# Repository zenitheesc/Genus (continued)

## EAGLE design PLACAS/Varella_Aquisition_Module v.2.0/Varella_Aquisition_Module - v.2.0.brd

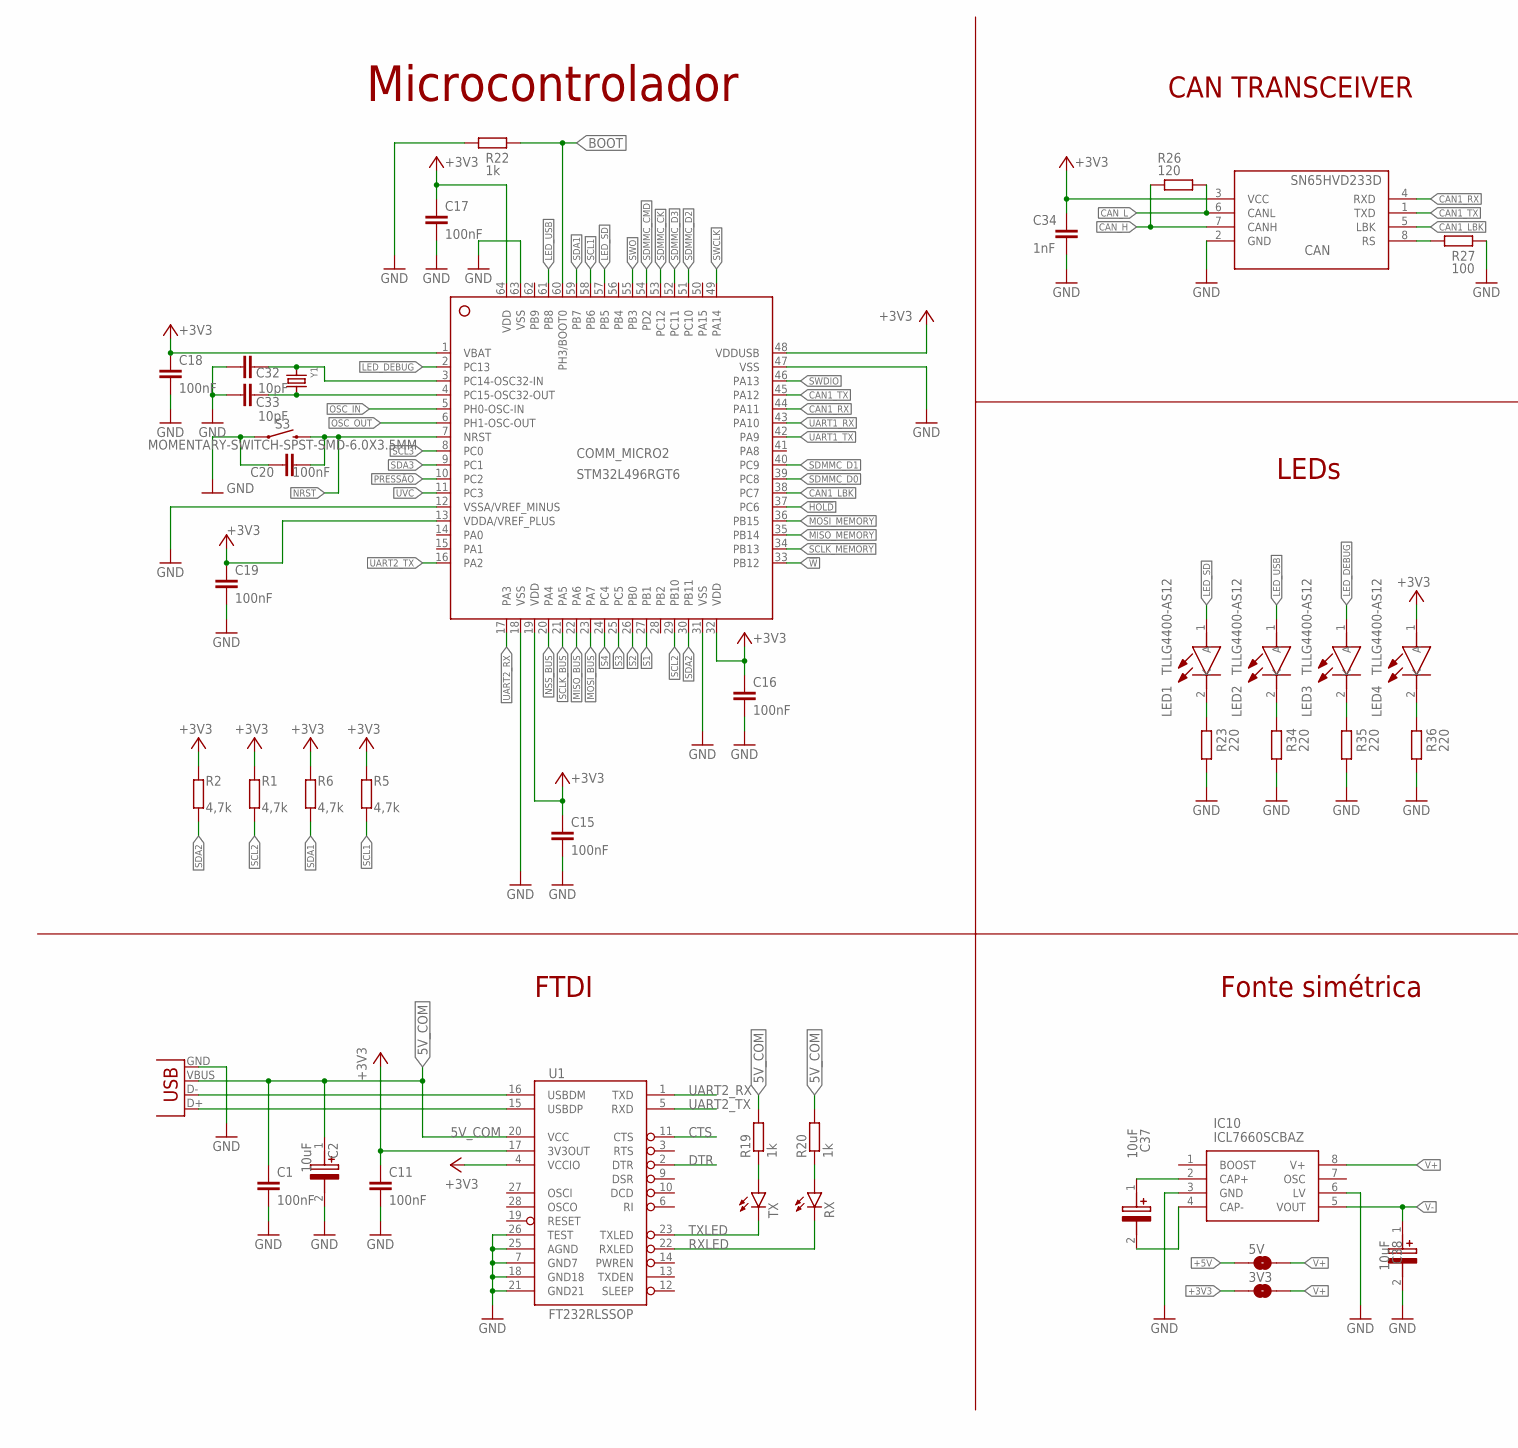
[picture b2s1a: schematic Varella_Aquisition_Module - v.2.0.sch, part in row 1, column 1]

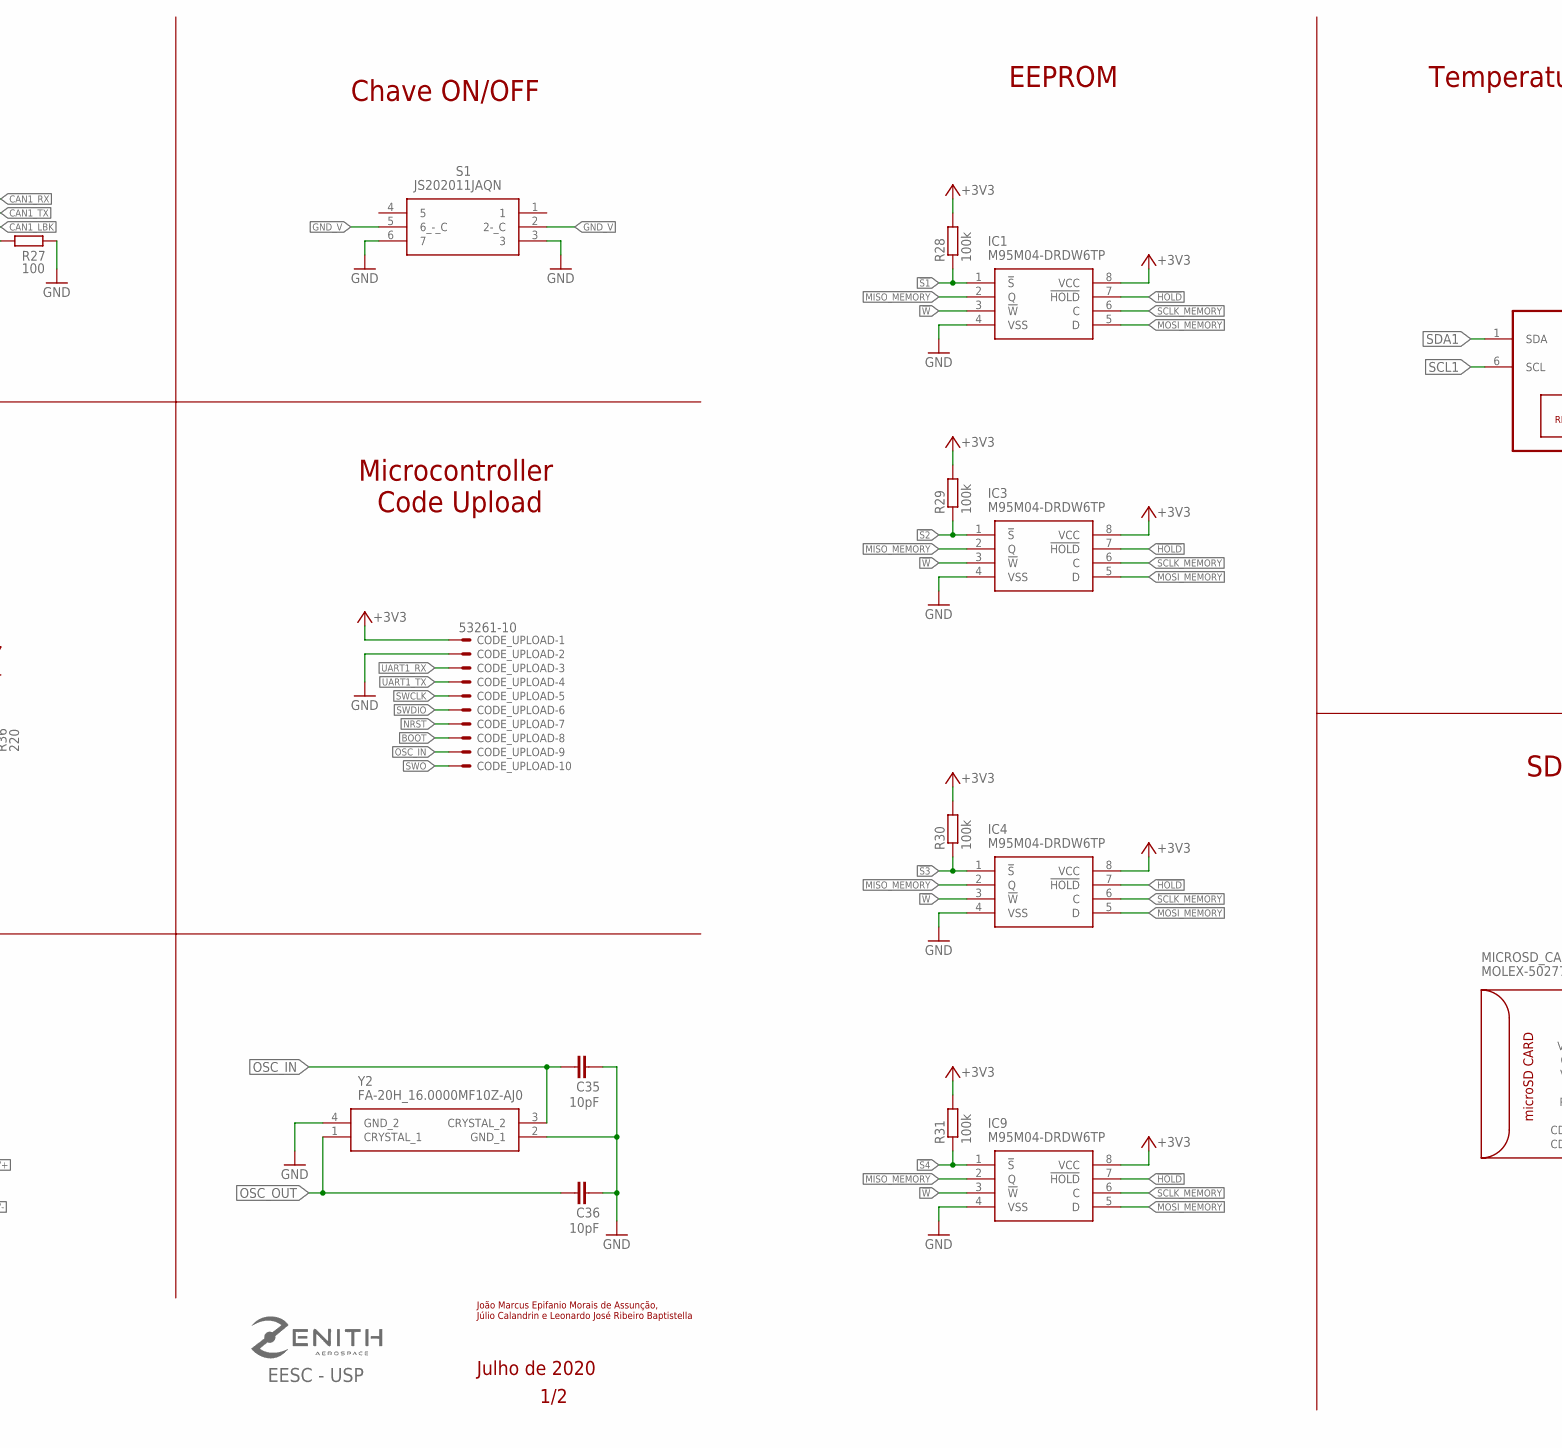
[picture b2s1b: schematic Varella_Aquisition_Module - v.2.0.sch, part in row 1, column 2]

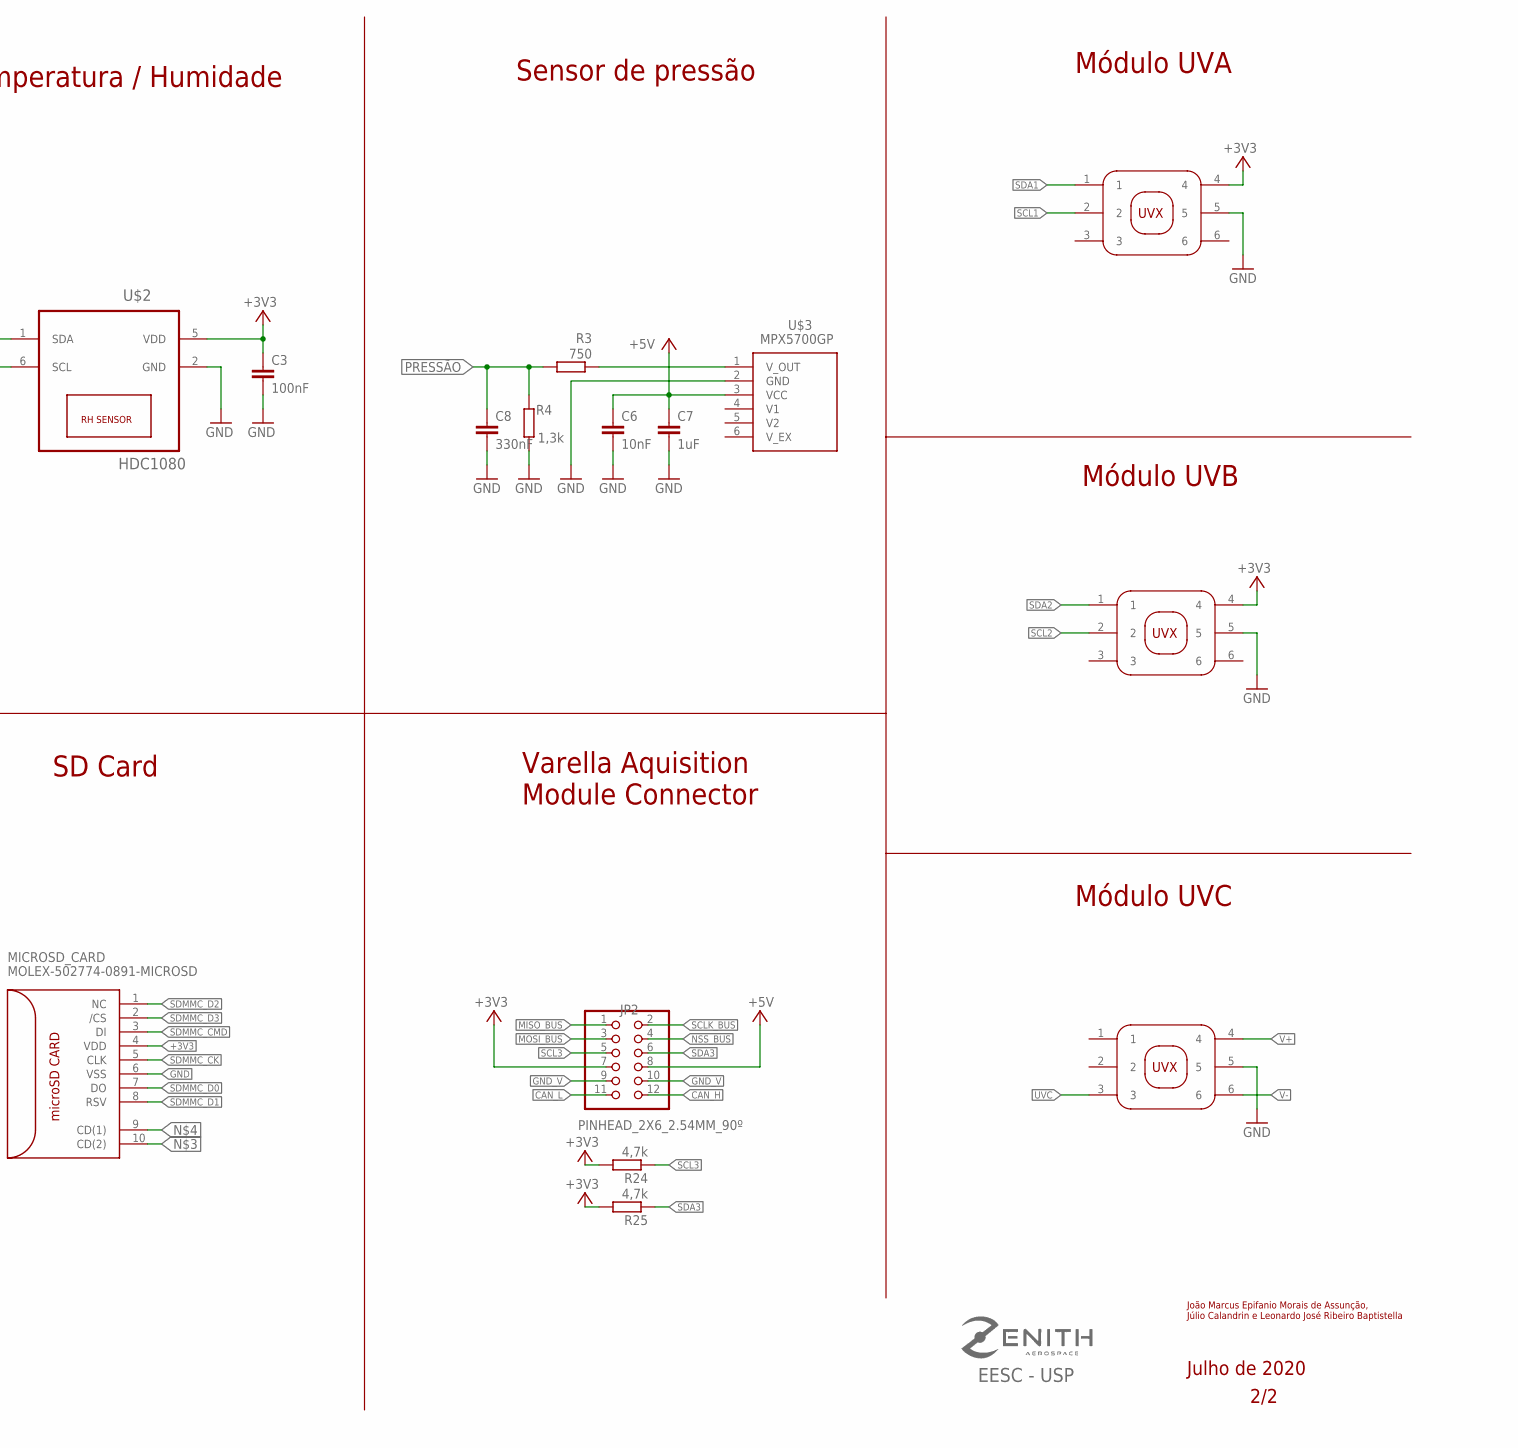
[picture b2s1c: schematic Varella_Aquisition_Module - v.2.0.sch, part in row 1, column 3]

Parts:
3V3, 5V: SMD-JUMPER-2
C1, C3, C11, C15, C16, C17, C18, C19, C20: 100nF; C0805
C2, C37, C38: 10uF; CAPAE430X610N
C6: 10nF; C0805
C7: 1uF; C0805
C8: 330nF; C0805
C32, C33, C35, C36: 10pF; C0805
C34: 1nF; C1206
CAN: SN65HVD233D; SOIC8
CODE_UPLOAD: 53261-10
COMM_MICRO2: STM32L496RGT6; LQFP64_10X10
IC1, IC3, IC4, IC9: M95M04-DRDW6TP; SOP65P640X120-8N
IC10: ICL7660SCBAZ; SOIC127P600X175-8N@1
JP2: PINHEAD_2X6_2.54MM_90º
LED1, LED2, LED3, LED4: TLLG4400-AS12; TLLG4400AS12
MICROSD_CARD: MOLEX-502774-0891-MICROSD
R1, R2, R5, R6, R24, R25: 4,7k; R0805
R3: 750; R0805
R4: 1,3k; R0805
R19, R20, R22: 1k; R0805
R23, R34, R35, R36: 220; R0805
R26: 120; R1206
R27: 100; R0805
R28, R29, R30, R31: 100k; R0805
RX: LEDCHIPLED_0805; CHIPLED_0805
S1: JS202011JAQN
S3: MOMENTARY-SWITCH-SPST-SMD-6.0X3.5MM; TACTILE_SWITCH_SMD_6.0X3.5MM
TX: LEDCHIPLED_0805; CHIPLED_0805
U1: FT232RLSSOP; SSOP28DB
U$2: HDC1080; TI-S-PWSON-N6
U$3: MPX5700GP
U$6, U$7, U$8: MODULO_UV
X2: USB-SMD-NS; USB-MINIB-NOSTOP
Y1: CRYSTAL8X3.8SMT; CRYSTAL_8X3.8
Y2: FA-20H_16.0000MF10Z-AJ0; FA20H160000MF12ZAC3

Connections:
5V_COM: C1.1, C2.1 (+), R19.2, R20.2, U1.20 (VCC), X2.VBUS
!HOLD: COMM_MICRO2.37 (PC6), IC1.7 (!HOLD), IC3.7 (!HOLD), IC4.7 (!HOLD), IC9.7 (!HOLD)
!S1: COMM_MICRO2.27 (PB1), IC1.1 (!S), R28.1
!S2: COMM_MICRO2.26 (PB0), IC3.1 (!S), R29.1
!S3: COMM_MICRO2.25 (PC5), IC4.1 (!S), R30.1
!S4: COMM_MICRO2.24 (PC4), IC9.1 (!S), R31.1
!W: COMM_MICRO2.33 (PB12), IC1.3 (!W), IC3.3 (!W), IC4.3 (!W), IC9.3 (!W)
+3V3: 3V3.2, C3.1, C11.1, C15.1, C16.1, C17.1, C18.1, C19.1, C34.1, CAN.3 (VCC), CODE_UPLOAD.1, COMM_MICRO2.1 (VBAT), COMM_MICRO2.13 (VDDA/VREF_PLUS), COMM_MICRO2.19 (VDD), COMM_MICRO2.32 (VDD), COMM_MICRO2.48 (VDDUSB), COMM_MICRO2.64 (VDD), IC1.8 (VCC), IC3.8 (VCC), IC4.8 (VCC), IC9.8 (VCC), JP2.7, LED4.1 (A), MICROSD_CARD.4 (VDD), R1.2, R2.2, R5.2, R6.2, R24.2, R25.2, R28.2, R29.2, R30.2, R31.2, U1.4 (VCCIO), U1.17 (3V3OUT), U$2.5 (VDD), U$6.4, U$7.4
+5V: 5V.2, C6.1, C7.1, JP2.8, U$3.3 (VCC)
BOOT: CODE_UPLOAD.8, COMM_MICRO2.60 (PH3/BOOT0), R22.1
CAN1_LBK: CAN.5 (LBK), COMM_MICRO2.38 (PC7)
CAN1_RX: CAN.4 (RXD), COMM_MICRO2.44 (PA11)
CAN1_TX: CAN.1 (TXD), COMM_MICRO2.45 (PA12)
CAN_H: CAN.7 (CANH), JP2.12, R26.1
CAN_L: CAN.6 (CANL), JP2.11, R26.2
CRYSTAL1: C32.2, COMM_MICRO2.3 (PC14-OSC32-IN), Y1.P$1 (1)
CTS: U1.11 (CTS)
DTR: U1.2 (DTR)
GND: C1.2, C2.2 (-), C3.2, C6.2, C7.2, C8.2, C11.2, C15.2, C16.2, C17.2, C18.2, C19.2, C20.1, C32.1, C33.1, C34.2, C35.2, C36.2, C38.2 (-), CAN.2 (GND), CODE_UPLOAD.2, COMM_MICRO2.12 (VSSA/VREF_MINUS), COMM_MICRO2.18 (VSS), COMM_MICRO2.31 (VSS), COMM_MICRO2.47 (VSS), COMM_MICRO2.63 (VSS), IC1.4 (VSS), IC3.4 (VSS), IC4.4 (VSS), IC9.4 (VSS), IC10.3 (GND), IC10.6 (LV), MICROSD_CARD.6 (VSS), R4.2, R22.2, R23.1, R27.1, R34.1, R35.1, R36.1, S1.3, S1.6 (7), S3.1, U1.7 (GND7), U1.18 (GND18), U1.21 (GND21), U1.25 (AGND), U1.26 (TEST), U$2.2 (GND), U$6.5, U$7.5, U$8.5, X2.GND, Y2.2 (GND_1), Y2.4 (GND_2)
GND_V: JP2.9, JP2.10, S1.2 (2-_C), S1.5 (6_-_C)
LED_DEBUG: COMM_MICRO2.2 (PC13), LED3.1 (A)
LED_SD: COMM_MICRO2.57 (PB5), LED1.1 (A)
LED_USB: COMM_MICRO2.61 (PB8), LED2.1 (A)
MISO_BUS: COMM_MICRO2.22 (PA6), JP2.1
MISO_MEMORY: COMM_MICRO2.35 (PB14), IC1.2 (Q), IC3.2 (Q), IC4.2 (Q), IC9.2 (Q)
MOSI_BUS: COMM_MICRO2.23 (PA7), JP2.3
MOSI_MEMORY: COMM_MICRO2.36 (PB15), IC1.5 (D), IC3.5 (D), IC4.5 (D), IC9.5 (D)
unnamed: R3.1, U$3.1 (V_OUT)
unnamed: C33.2, COMM_MICRO2.4 (PC15-OSC32-OUT), Y1.P$4 (2)
unnamed: CAN.8 (RS), R27.2
unnamed: C37.1 (+), IC10.2 (CAP+)
unnamed: C37.2 (-), IC10.4 (CAP-)
unnamed: LED1.2 (K), R23.2
unnamed: LED2.2 (K), R34.2
unnamed: LED3.2 (K), R35.2
unnamed: LED4.2 (K), R36.2
NRST: C20.2, CODE_UPLOAD.7, COMM_MICRO2.7 (NRST), S3.2
NSS_BUS: COMM_MICRO2.20 (PA4), JP2.4
OSC_IN: C35.1, CODE_UPLOAD.9, COMM_MICRO2.5 (PH0-OSC-IN), Y2.3 (CRYSTAL_2)
OSC_OUT: C36.1, COMM_MICRO2.6 (PH1-OSC-OUT), Y2.1 (CRYSTAL_1)
PRESSÃO: C8.1, COMM_MICRO2.10 (PC2), R3.2, R4.1
RXL: R20.1, RX.A
RXLED: RX.C, U1.22 (RXLED)
SCL1: COMM_MICRO2.58 (PB6), R5.1, U$2.6 (SCL), U$6.2
SCL2: COMM_MICRO2.29 (PB10), R1.1, U$7.2
SCL3: COMM_MICRO2.8 (PC0), JP2.5, R24.1
SCLK_BUS: COMM_MICRO2.21 (PA5), JP2.2
SCLK_MEMORY: COMM_MICRO2.34 (PB13), IC1.6 (C), IC3.6 (C), IC4.6 (C), IC9.6 (C)
SDA1: COMM_MICRO2.59 (PB7), R6.1, U$2.1 (SDA), U$6.1
SDA2: COMM_MICRO2.30 (PB11), R2.1, U$7.1
SDA3: COMM_MICRO2.9 (PC1), JP2.6, R25.1
SDMMC_CK: COMM_MICRO2.53 (PC12), MICROSD_CARD.5 (CLK)
SDMMC_CMD: COMM_MICRO2.54 (PD2), MICROSD_CARD.3 (DI)
SDMMC_D0: COMM_MICRO2.39 (PC8), MICROSD_CARD.7 (DO)
SDMMC_D1: COMM_MICRO2.40 (PC9), MICROSD_CARD.8 (RSV)
SDMMC_D2: COMM_MICRO2.51 (PC10), MICROSD_CARD.1 (NC)
SDMMC_D3: COMM_MICRO2.52 (PC11), MICROSD_CARD.2 (/CS)
SWCLK: CODE_UPLOAD.5, COMM_MICRO2.49 (PA14)
SWDIO: CODE_UPLOAD.6, COMM_MICRO2.46 (PA13)
SWO: CODE_UPLOAD.10, COMM_MICRO2.55 (PB3)
TXL: R19.1, TX.A
TXLED: TX.C, U1.23 (TXLED)
UART1_RX: CODE_UPLOAD.3, COMM_MICRO2.43 (PA10)
UART1_TX: CODE_UPLOAD.4, COMM_MICRO2.42 (PA9)
UART2_RX: COMM_MICRO2.17 (PA3), U1.1 (TXD)
UART2_TX: COMM_MICRO2.16 (PA2), U1.5 (RXD)
USB_D+2: U1.15 (USBDP), X2.D+
USB_D-2: U1.16 (USBDM), X2.D-
UVC: COMM_MICRO2.11 (PC3), U$8.3
V+: 3V3.1, 5V.1, IC10.8 (V+), U$8.4
V-: C38.1 (+), IC10.5 (VOUT), U$8.6

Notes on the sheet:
C:/Users/marcu/Desktop/Ensino Superior/Graduação - Eng Elétrica/Zenith/zenith-v2.bmp
Microcontrolador
CAN TRANSCEIVER
Microcontroller Code Upload
SD Card
Varella Aquisition Module Connector
EEPROM
FTDI
Temperatura / Humidade
Fonte simétrica
LEDs
Sensor de pressão
Chave ON/OFF
Módulo UVA
Módulo UVB
Módulo UVC
EESC - USP
Julho de 2020
2/2
1/2
João Marcus Epifanio Morais de Assunção, Júlio Calandrin e Leonardo José Ribeiro Baptistella

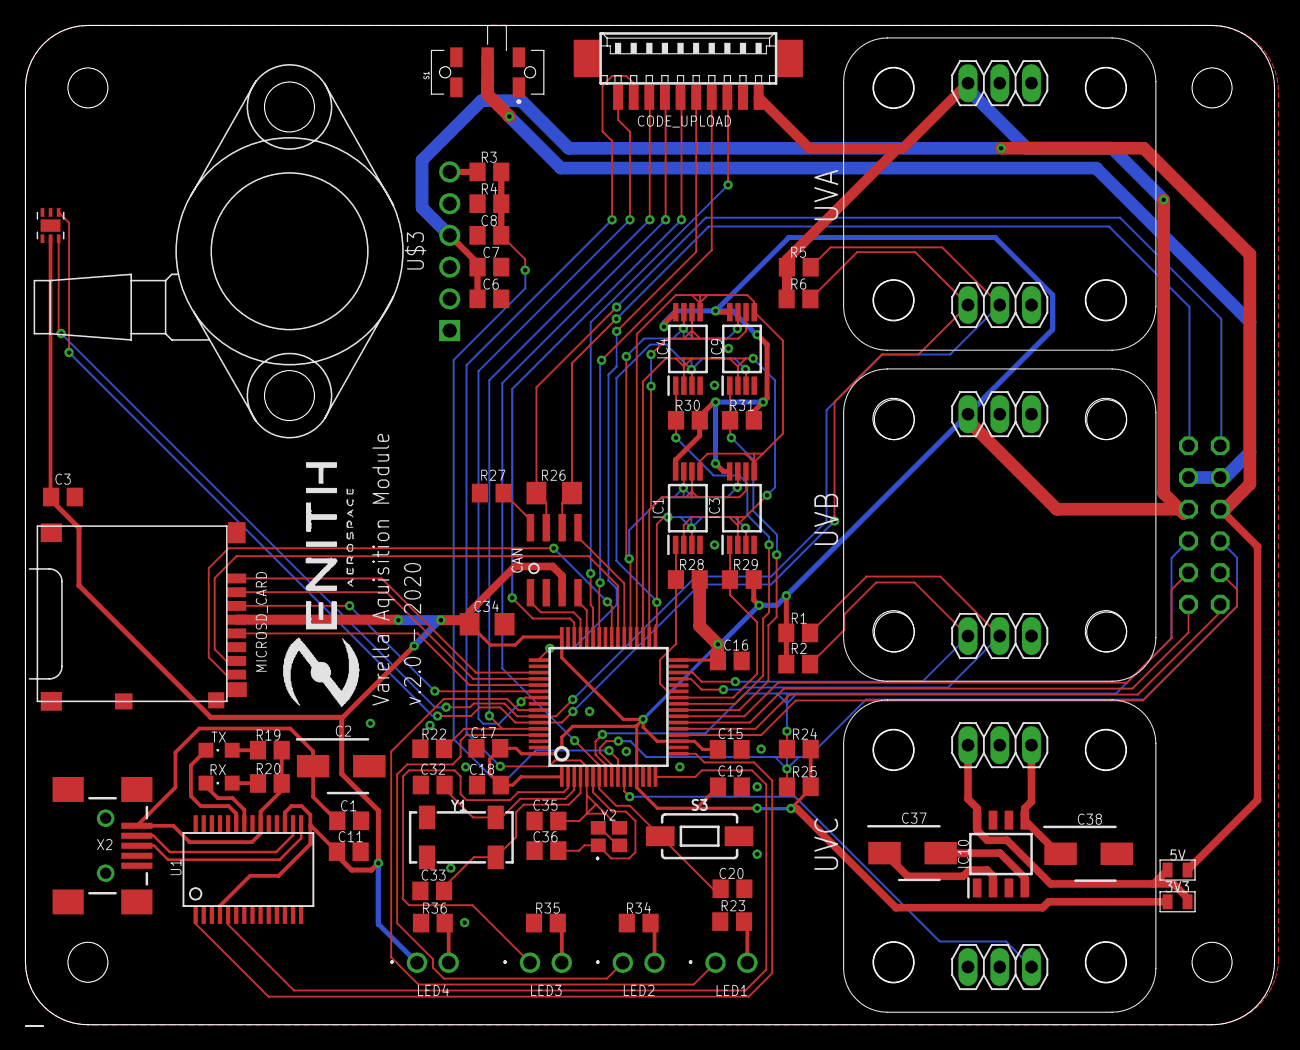
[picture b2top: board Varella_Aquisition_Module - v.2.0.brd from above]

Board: 2 copper layers, 100.0 x 80.0 mm, 70 parts (1 on the bottom side), 69 nets.

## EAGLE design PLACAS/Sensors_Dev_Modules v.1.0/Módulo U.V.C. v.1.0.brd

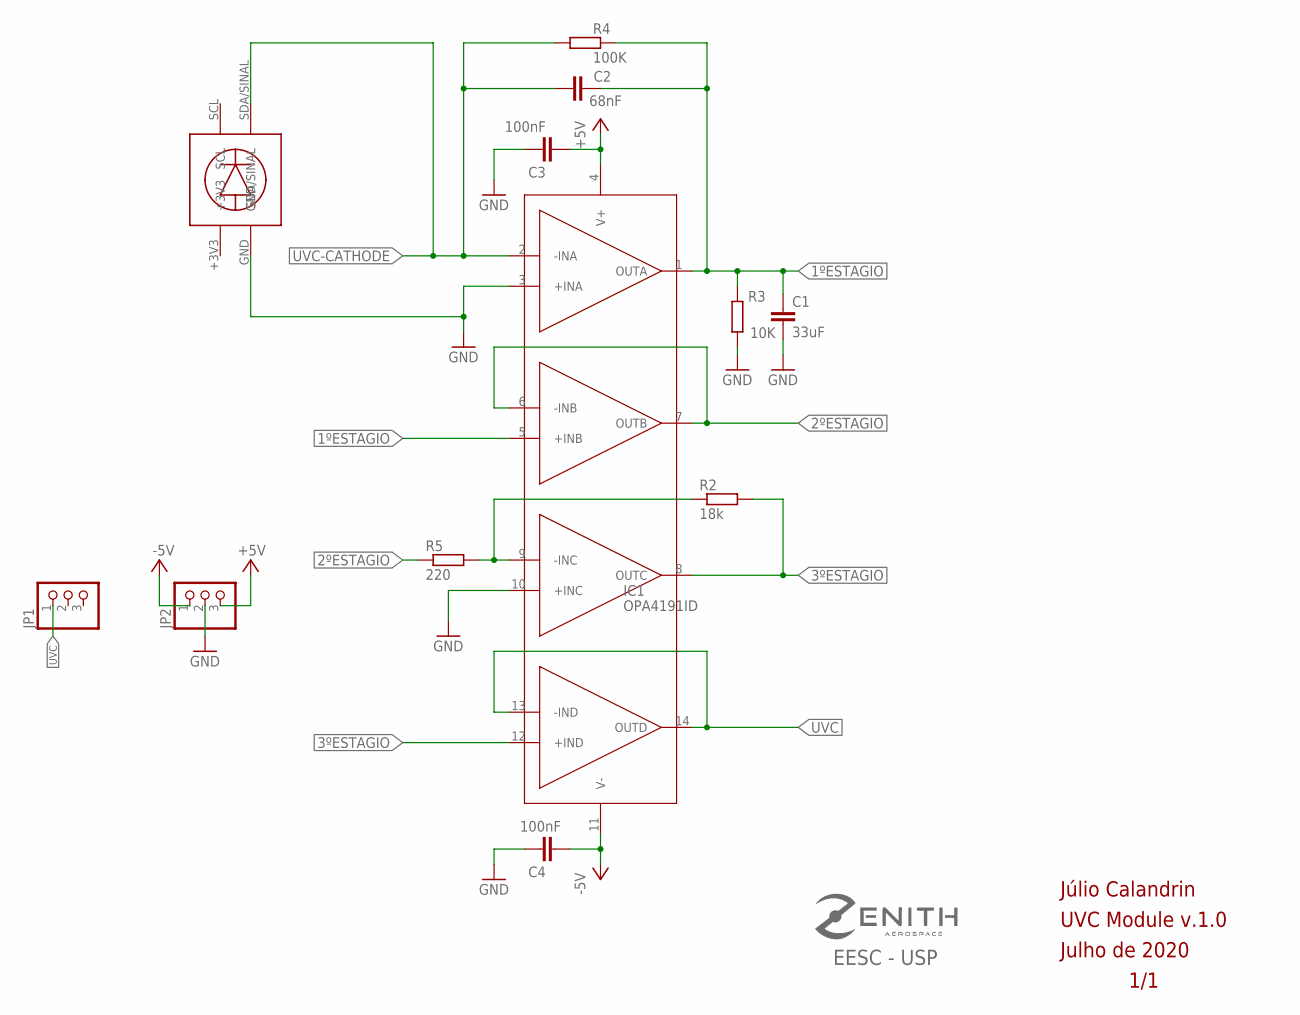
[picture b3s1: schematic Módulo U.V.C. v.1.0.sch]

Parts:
C1: 33uF; C0805
C2: 68nF; C0805
C3, C4: 100nF; C0805
IC1: OPA4191ID; D14_TEX
JP1, JP2: PINHD-1X3; 1X03
R2: 18k; R0805
R3: 10K; R0805
R4: 100K; R0805
R5: 220; R0805
U$3: UNIVERSAL_BREAKOUT; UNIVERSAL_PADS

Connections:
1ºESTAGIO: C1.1, C2.2, IC1.1 (OUTA), IC1.5 (+INB), R3.2, R4.2
2ºESTAGIO: IC1.6 (-INB), IC1.7 (OUTB), R5.1
3ºESTAGIO: IC1.8 (OUTC), IC1.12 (+IND), R2.2
+5V: C3.1, IC1.4 (V+), JP2.3
-5V: C4.1, IC1.11 (V-), JP2.1
GND: C1.2, C3.2, C4.2, IC1.3 (+INA), IC1.10 (+INC), JP2.2, R3.1, U$3.GND
unnamed: IC1.9 (-INC), R2.1, R5.2
UVC: IC1.13 (-IND), IC1.14 (OUTD), JP1.1
UVC-CATHODE: C2.1, IC1.2 (-INA), R4.1, U$3.SDA/SINAL

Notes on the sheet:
EESC - USP
Júlio Calandrin
Julho de 2020
1/1
UVC Module v.1.0

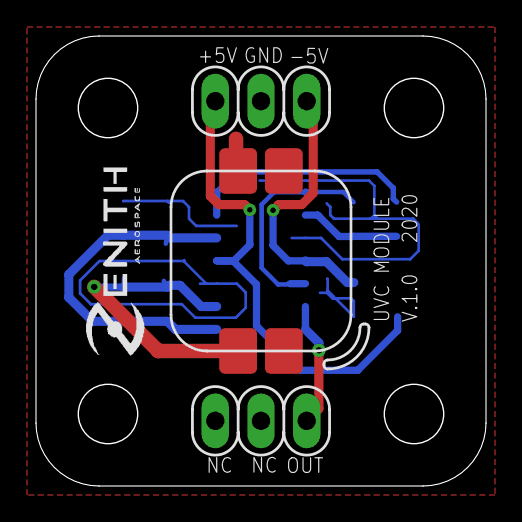
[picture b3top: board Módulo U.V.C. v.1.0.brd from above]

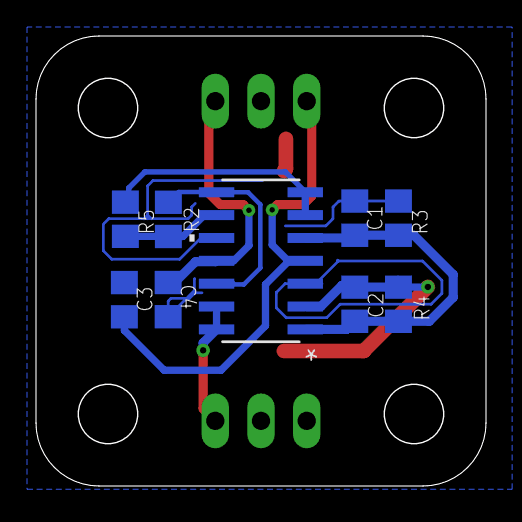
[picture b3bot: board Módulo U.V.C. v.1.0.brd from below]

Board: 2 copper layers, 25.0 x 25.0 mm, 12 parts (9 on the bottom side), 9 nets.

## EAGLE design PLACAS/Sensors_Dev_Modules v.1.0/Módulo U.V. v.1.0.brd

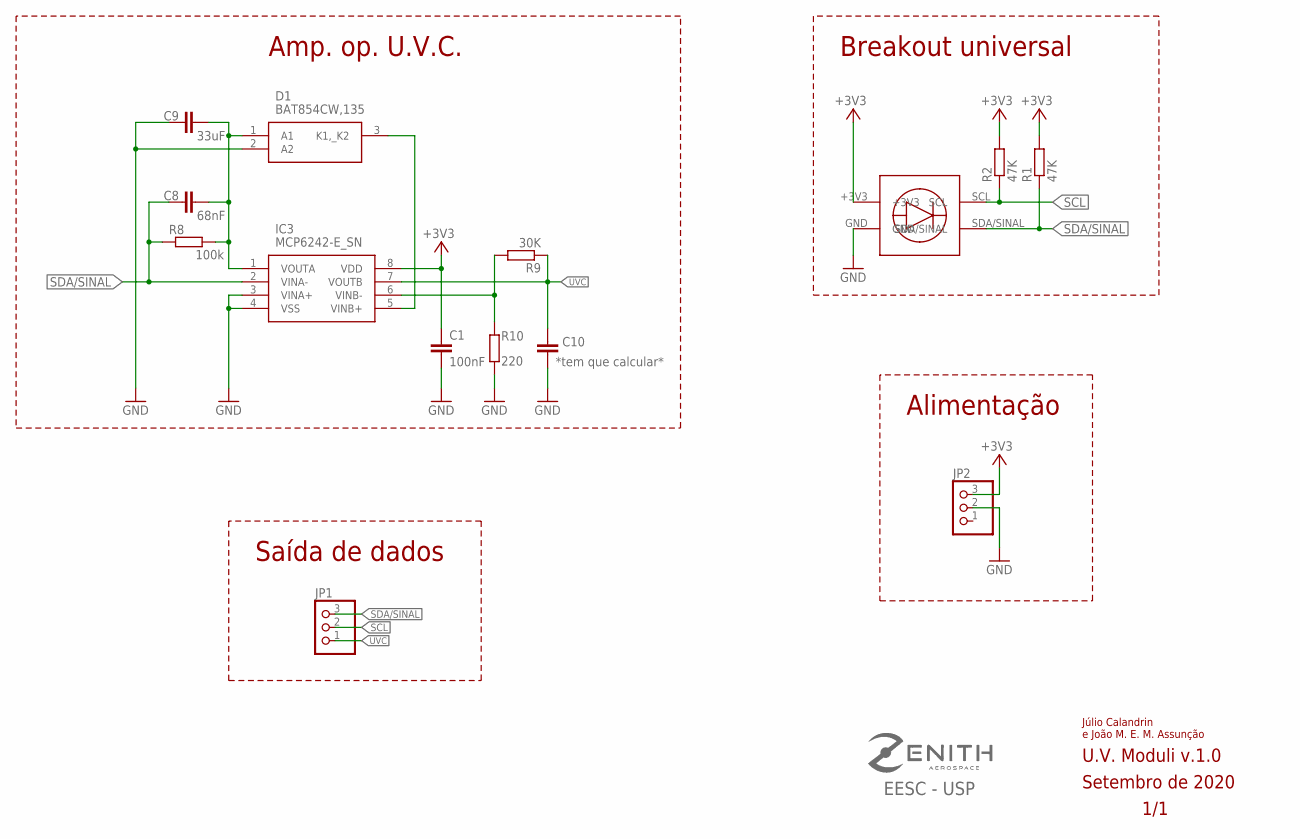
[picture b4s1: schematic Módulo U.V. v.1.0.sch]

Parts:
C1: 100nF; C0805
C8: 68nF; C0805
C9: 33uF; C0805
C10: *tem que calcular*; C0805
D1: BAT854CW,135; SOT65P210X110-3N
IC3: MCP6242-E_SN; SOIC127P600X175-8N
JP1, JP2: PINHD-1X3; 1X03
R1, R2: 47K; R0805
R8: 100k; R0805
R9: 30K; R0805
R10: 220; R0805
U$1: UNIVERSAL_BREAKOUT; UNIVERSAL_PADS

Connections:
+3V3: C1.1, IC3.8 (VDD), JP2.3, R1.2, R2.2, U$1.+3V3
GND: C1.2, C9.2, C10.2, D1.2 (A2), IC3.3 (VINA+), IC3.4 (VSS), JP2.2, R10.1, U$1.GND
unnamed: C8.2, C9.1, D1.1 (A1), IC3.1 (VOUTA), R8.2
unnamed: D1.3 (K1,_K2), IC3.5 (VINB+)
unnamed: IC3.6 (VINB-), R9.2, R10.2
SCL: JP1.2, R2.1, U$1.SCL
SDA/SINAL: C8.1, IC3.2 (VINA-), JP1.3, R1.1, R8.1, U$1.SDA/SINAL
UVC: C10.1, IC3.7 (VOUTB), JP1.1, R9.1

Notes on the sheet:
EESC - USP
Júlio Calandrin e João M. E. M. Assunção
Setembro de 2020
1/1
U.V. Moduli v.1.0
Amp. op. U.V.C.
Breakout universal
Saída de dados
Alimentação

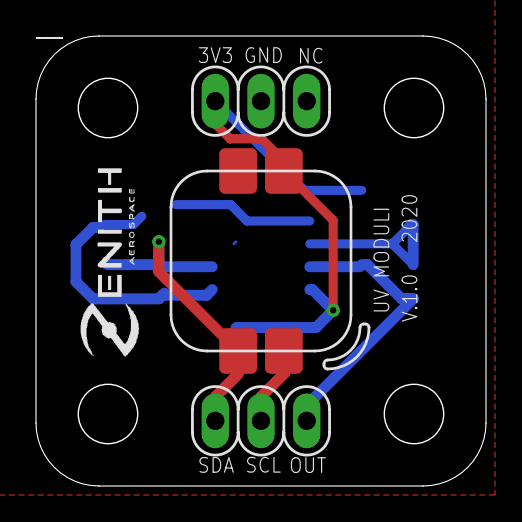
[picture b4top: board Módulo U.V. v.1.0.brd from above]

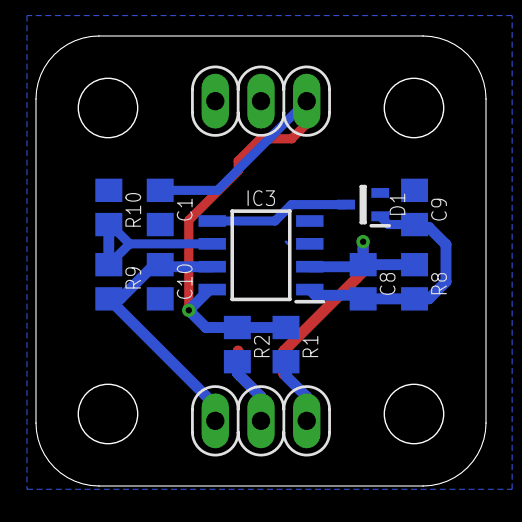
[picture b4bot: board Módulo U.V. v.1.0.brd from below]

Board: 2 copper layers, 25.0 x 25.0 mm, 14 parts (11 on the bottom side), 8 nets.

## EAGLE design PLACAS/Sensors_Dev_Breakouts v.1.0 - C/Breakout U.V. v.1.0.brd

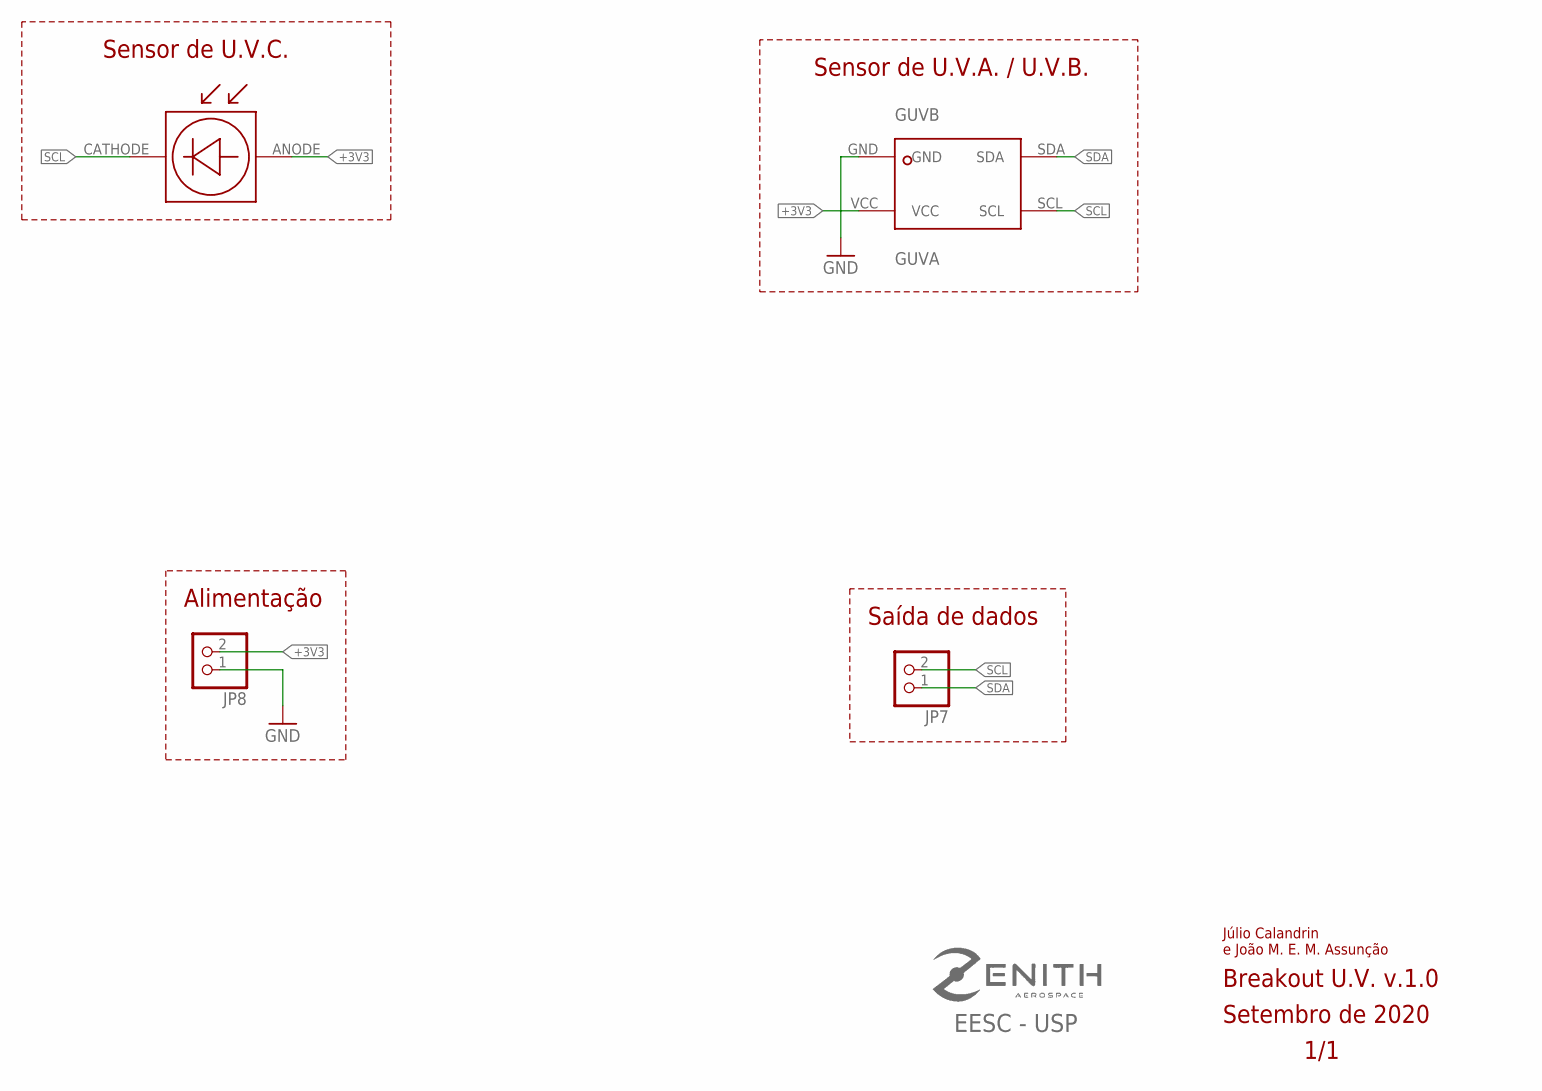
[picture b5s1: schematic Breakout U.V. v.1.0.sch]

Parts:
GUVB: GUVA; GUV_A/B
JP7, JP8: PINHD-1X2; 1X02(PAD_REDUZIDO)
U$1: GUVC-S10GD; GUV_C

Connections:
+3V3: GUVB.VCC, JP8.2, U$1.ANODE
GND: GUVB.GND, JP8.1
SCL: GUVB.SCL, JP7.2, U$1.CATHODE
SDA: GUVB.SDA, JP7.1

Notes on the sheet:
EESC - USP
Júlio Calandrin e João M. E. M. Assunção
Setembro de 2020
1/1
Breakout U.V. v.1.0
Sensor de U.V.C.
Sensor de U.V.A. / U.V.B.
Alimentação
Saída de dados

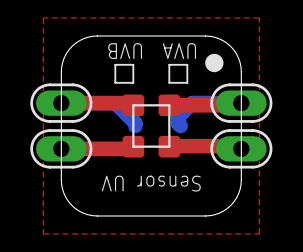
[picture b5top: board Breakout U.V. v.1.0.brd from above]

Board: 2 copper layers, 10.0 x 10.0 mm, 4 parts (1 on the bottom side), 4 nets.

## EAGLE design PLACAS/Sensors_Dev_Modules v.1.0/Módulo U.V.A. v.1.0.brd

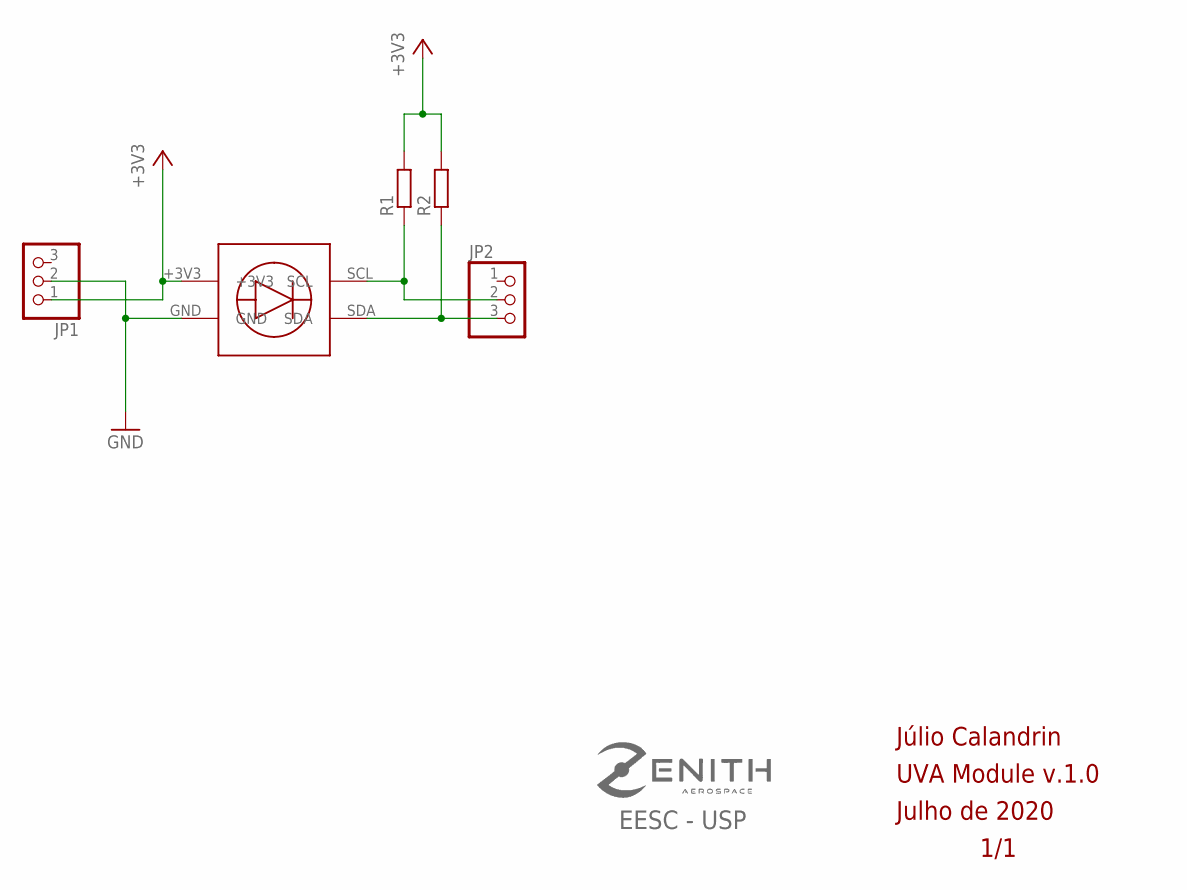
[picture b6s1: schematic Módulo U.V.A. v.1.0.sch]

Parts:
JP1, JP2: PINHD-1X3; 1X03
R1, R2: R-EU_R0805; R0805
U$1: BREAKOUT_UV-A; PADS_UV-A/B

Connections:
+3V3: JP1.1, R1.2, R2.2, U$1.+3V3
GND: JP1.2, U$1.GND
unnamed: JP2.3, R2.1, U$1.SDA
unnamed: JP2.2, R1.1, U$1.SCL

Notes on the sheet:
EESC - USP
Júlio Calandrin
Julho de 2020
1/1
UVA Module v.1.0

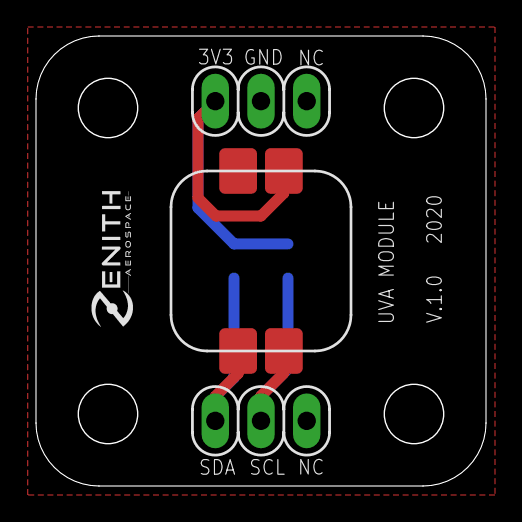
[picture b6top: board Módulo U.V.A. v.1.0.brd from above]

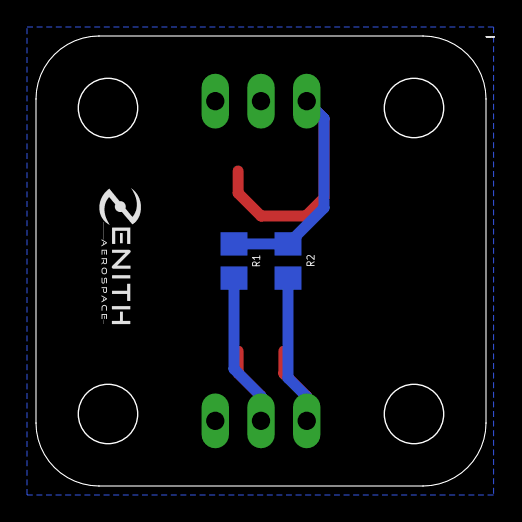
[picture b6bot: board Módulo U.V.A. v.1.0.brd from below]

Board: 2 copper layers, 25.0 x 25.0 mm, 5 parts (2 on the bottom side), 4 nets.

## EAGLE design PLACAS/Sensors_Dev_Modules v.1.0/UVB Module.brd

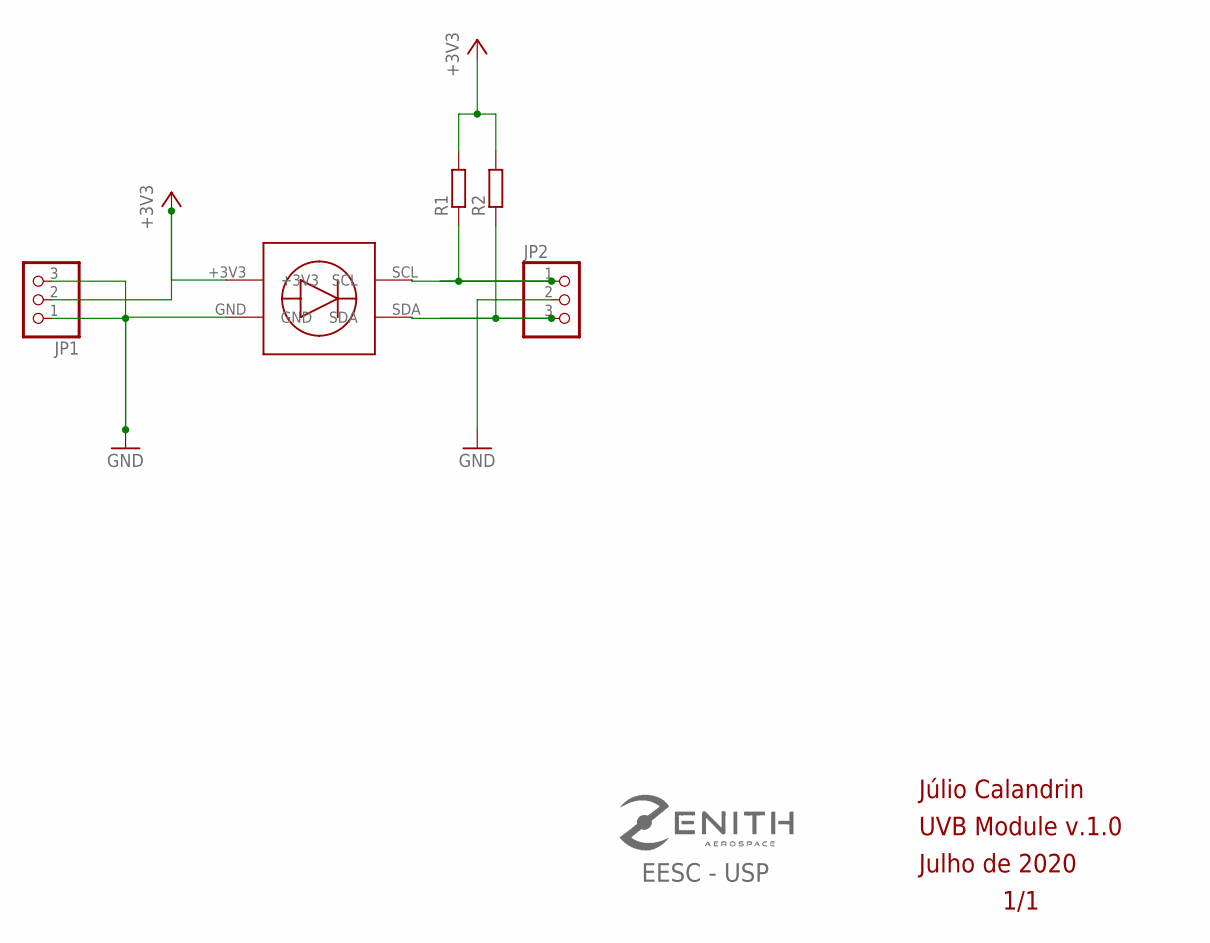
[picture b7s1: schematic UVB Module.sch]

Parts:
JP1, JP2: PINHD-1X3; 1X03
R1, R2: R-EU_R0805; R0805
U$1: BREAKOUT_UV-B; PADS_UV-A/B

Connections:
+3V3: JP1.2, R1.2, R2.2, U$1.+3V3
GND: JP1.1, JP1.3, JP2.2, U$1.GND
unnamed: JP2.3, R2.1, U$1.SDA
unnamed: JP2.1, R1.1, U$1.SCL

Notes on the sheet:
EESC - USP
Júlio Calandrin
Julho de 2020
1/1
UVB Module v.1.0

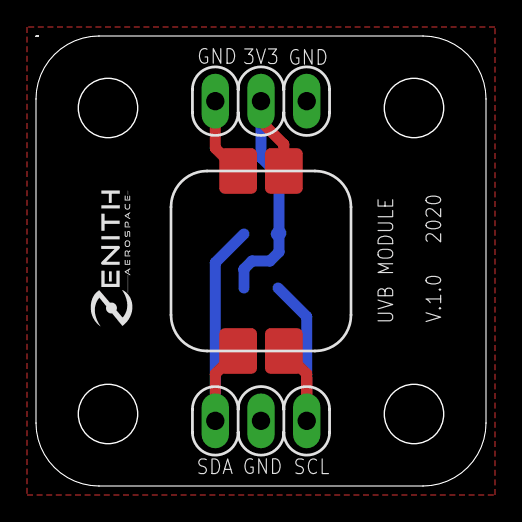
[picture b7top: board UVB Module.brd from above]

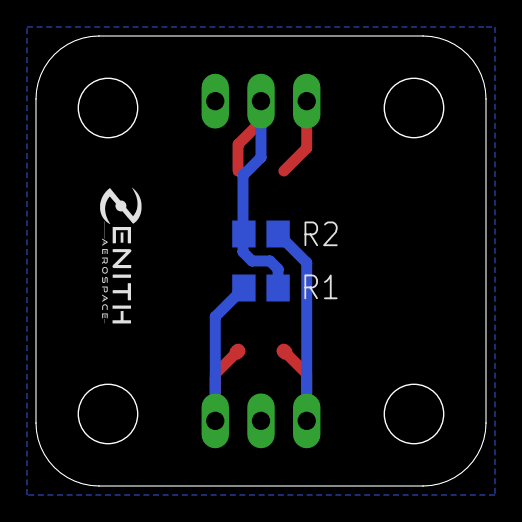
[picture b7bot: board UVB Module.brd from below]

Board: 2 copper layers, 25.0 x 25.0 mm, 5 parts (2 on the bottom side), 4 nets.

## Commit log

2020-06-07 first
2020-06-07 Revert "first"
    This reverts commit eb21f9ab56f20263a839bdc1a0050135d5b35093.
2020-06-07 feature
2020-06-07 libaries
2020-06-07 Last
2020-06-09 Libraries
2020-06-11 Created README.md with link to WIKI
2020-06-22 conectores
2020-06-22 test
2020-06-25 dbls
2020-07-24 Alteração nos design blocks
2020-08-02 design block change
2020-08-02 removed
2020-09-11 Create Genus_MainBoard_Lite-v.1.0.b##
2021-02-13 Added 3D gif
2021-02-28 Rename .github/dynamic-readme.yaml to .github/workflows/dynamic-readme.yaml
2021-02-28 💬 - File Rebuilt | Github Action Runner : 1
2021-02-28 Create LICENSE
2021-03-01 README super estilizado
2021-03-01 README.md: centered images
